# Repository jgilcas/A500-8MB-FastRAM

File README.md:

# A500-8MB-FastRAM

Okay - this is a fusion of the 8MB FastRAM Board for the Amiga 500 &amp; Amiga 500+, and the 14MHz Accelerator. 

This board is based on the A600 8MB FastRAM board here: http://lvd.nedopc.com/Projects/a600_8mb/index.html and the accelerator schematic designed by Livio Plos and released into the wild in 1992.

As such, the schematic is a derivative/fork of the original designs, to accommodate it's usage in A500's (might also work in A1000's & A2000's but it's untested).

Everything has been designed to be as easy to solder as possible. Yes, it is all SMT components but these are SOIC & SOJ for the IC's and 1206 parts with hand solder pads for the capacitors and resistors. This should be easily accomplished with a cheap soldering iron like the Yihua 937D (A Hakko knockoff from china, usually costs around £40)

The code for the CPLD has been mostly unchanged from the original, just a single letter changed to reflect usage in the A500 as opposed to the A600, along with renaming the signal pins to something simpler.

There is only 16 Mb of addressable space on 68000 CPU. This board uses half of that space, residing at $200000-$9FFFFF address range. It does autoconfigure, so no need to do anything in the DOS shell.

The original design used an Altera EPM7032 5v CPLD - this has been changed for an Atmel ATF1502ASV - as these are pin-compatible replacements. 

# Bill of Materials

-= COMING SOON =-

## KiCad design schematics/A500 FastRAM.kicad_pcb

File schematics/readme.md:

This project was created in KiCad 5.1.2 - all the files you need to build this project have been added here.

You'll need the custom library files at the very least.

I've included the SPECTRA DSN export from KiCad and the Freerouter Session file as a baseline.

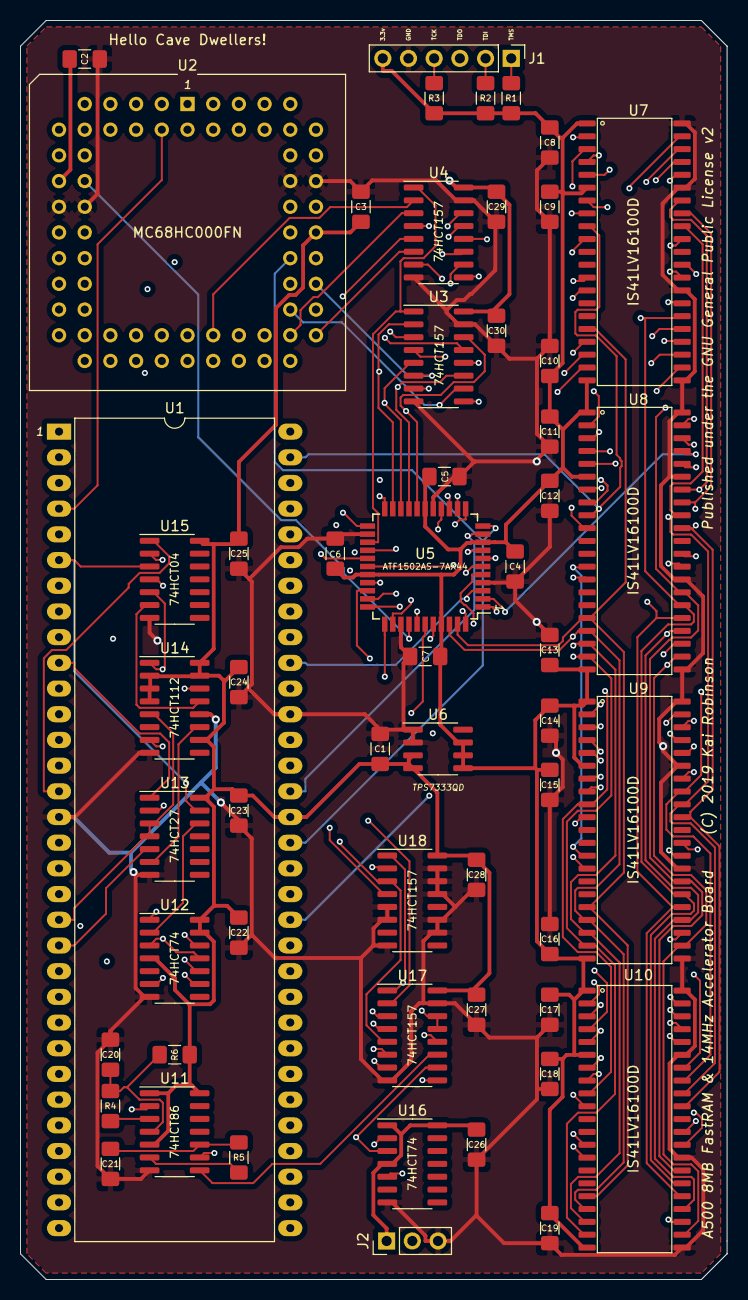
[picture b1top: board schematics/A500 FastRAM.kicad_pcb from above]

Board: 4 copper layers, 69.9 x 124.5 mm, 56 parts (0 on the bottom side), 105 nets.

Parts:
C1, C2, C3, C4, C5, C6, C7, C8, C9, C10, C11, C12, C13, C14, C15, C16, C17, C18, C19, C22, C23, C24, C25, C26, C27, C28, C29, C30: 0.1uF; C_1206_3216Metric_Pad1.42x1.75mm_HandSolder
C20, C21: 22pf; C_1206_3216Metric_Pad1.42x1.75mm_HandSolder
J1: Conn_01x06_Male; PinHeader_1x06_P2.54mm_Vertical
J2: Speed Selector; PinHeader_1x03_P2.54mm_Vertical
R1, R2, R3, R6: 10k; R_1206_3216Metric_Pad1.42x1.75mm_HandSolder
R4, R5: 560; R_1206_3216Metric_Pad1.42x1.75mm_HandSolder
U1: 68000 Boardside; DIP-64_W22.86mm_LongPads
U2: MC68000FN; PLCC-68_THT-Socket
U3, U4: 74157; SOIC-16_3.9x9.9mm_P1.27mm
U5: ATF1502AS-7AX44; TQFP-44_10x10mm_P0.8mm
U6: TPS7333QD; SOIC-8_3.9x4.9mm_P1.27mm
U7, U8, U9, U10: IS41LV16100D; SOJ-42
U11: 74HC86; SOIC-14_3.9x8.7mm_P1.27mm
U12, U16: 74HC74; SOIC-14_3.9x8.7mm_P1.27mm
U13: 74LS27; SOIC-14_3.9x8.7mm_P1.27mm
U14: 74LS112; SOIC-16_3.9x9.9mm_P1.27mm
U15: 74HC04; SOIC-14_3.9x8.7mm_P1.27mm
U17, U18: 74LS157; SOIC-16_3.9x9.9mm_P1.27mm

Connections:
/A500 FastRAM Page 3/CDAC: C21.2, R5.1, U11.10
/A500 FastRAM Page 3/SEL_SW: U16.5, U17.1, U18.1
/A500 FastRAM Page 3/SPD_SEL: J2.2, U16.2
/A500 FastRAM Page 3/SW_CLK14: U11.8, U17.11
/A500 FastRAM Page 3/SW_E14: U14.1, U15.5, U17.2
/A500 FastRAM Page 3/SW_VMA: U14.7, U17.5, U18.3
/A500 FastRAM Page 3/_CLKIN: U12.3, U12.11, U15.2
/A500 FastRAM Page 3/_E_OUT: U14.13, U15.6
/CPU_A1: U1.29, U2.32, U5.23
/CPU_A2: U1.30, U2.33, U5.22
/CPU_A3: U1.31, U2.34, U3.2, U5.21
/CPU_A4: U1.32, U2.35, U3.5, U5.20
/CPU_A5: U1.33, U2.36, U3.11, U5.19
/CPU_A6: U1.34, U2.37, U3.14, U5.18
/CPU_A7: U1.35, U2.38, U4.2
/CPU_A8: U1.36, U2.39, U4.5
/CPU_A9: U1.37, U2.40, U4.11
/CPU_A10: U1.38, U2.41, U4.14
/CPU_A11: U1.39, U2.42, U4.13
/CPU_A12: U1.40, U2.43, U4.10
/CPU_A13: U1.41, U2.44, U4.6
/CPU_A14: U1.42, U2.45, U4.3
/CPU_A15: U1.43, U2.46, U3.13
/CPU_A16: U1.44, U2.47, U3.10, U5.15
/CPU_A17: U1.45, U2.48, U3.6, U5.14
/CPU_A18: U1.46, U2.49, U3.3, U5.13
/CPU_A19: U1.47, U2.50, U5.12
/CPU_A20: U1.48, U2.51, U5.11
/CPU_A21: U1.50, U2.53, U5.10
/CPU_A22: U1.51, U2.54, U5.8
/CPU_A23: U1.52, U2.55, U5.6
/CPU_AS: U1.6, U12.12, U13.13, U15.3, U17.13, U17.14
/CPU_AS14: U2.6, U5.40, U17.12
/CPU_BERR: U1.22, U2.24
/CPU_BG: U1.11, U2.11
/CPU_BGACK: U1.12, U2.12
/CPU_BR: U1.13, U2.13
/CPU_CLK: U1.15, U11.2, U11.9, U15.1, U16.3, U17.10
/CPU_CLK14: U2.15, U5.37, U17.9
/CPU_D0: U1.5, U2.5, U7.2, U8.2, U9.2, U10.2
/CPU_D1: U1.4, U2.4, U7.3, U8.3, U9.3, U10.3
/CPU_D2: U1.3, U2.3, U7.4, U8.4, U9.4, U10.4
/CPU_D3: U1.2, U2.2, U7.5, U8.5, U9.5, U10.5
/CPU_D4: U1.1, U2.1, U7.7, U8.7, U9.7, U10.7
/CPU_D5: U1.64, U2.68, U7.8, U8.8, U9.8, U10.8
/CPU_D6: U1.63, U2.67, U7.9, U8.9, U9.9, U10.9
/CPU_D7: U1.62, U2.66, U7.10, U8.10, U9.10, U10.10
/CPU_D8: U1.61, U2.65, U7.33, U8.33, U9.33, U10.33
/CPU_D9: U1.60, U2.64, U7.34, U8.34, U9.34, U10.34
/CPU_D10: U1.59, U2.63, U7.35, U8.35, U9.35, U10.35
/CPU_D11: U1.58, U2.62, U7.36, U8.36, U9.36, U10.36
/CPU_D12: U1.57, U2.61, U5.44, U7.38, U8.38, U9.38, U10.38
/CPU_D13: U1.56, U2.60, U5.2, U7.39, U8.39, U9.39, U10.39
/CPU_D14: U1.55, U2.59, U5.3, U7.40, U8.40, U9.40, U10.40
/CPU_D15: U1.54, U2.58, U5.5, U7.41, U8.41, U9.41, U10.41
/CPU_DTACK: U1.10, U13.1
/CPU_DTACK14: U2.10, U12.6
/CPU_E: U1.20, U13.3, U13.4, U14.5, U17.3
/CPU_E14: U2.22, U17.4
/CPU_FC0: U1.28, U2.30
/CPU_FC1: U1.27, U2.29
/CPU_FC2: U1.26, U2.28
/CPU_HALT: U1.17, U2.19
/CPU_IPL0: U1.25, U2.27
/CPU_IPL1: U1.24, U2.26
/CPU_IPL2: U1.23, U2.25
/CPU_LDS: U1.8, U2.8, U5.27
/CPU_RESET: U1.18, U2.20, U5.39
/CPU_RW: U1.9, U2.9, U7.13, U8.13, U9.13, U10.13
/CPU_UDS: U1.7, U2.7, U5.38
/CPU_VMA: U1.19, U18.2
/CPU_VMA14: U2.21, U18.4
/CPU_VPA: U1.21, U13.5, U17.6
/CPU_VPA14: U2.23, U17.7
/DRAM_A0: U5.43, U7.17, U8.17, U9.17, U10.17
/DRAM_A1: U5.42, U7.18, U8.18, U9.18, U10.18
/DRAM_A2: U3.4, U7.19, U8.19, U9.19, U10.19
/DRAM_A3: U3.7, U7.20, U8.20, U9.20, U10.20
/DRAM_A4: U3.9, U7.23, U8.23, U9.23, U10.23
/DRAM_A5: U3.12, U7.24, U8.24, U9.24, U10.24
/DRAM_A6: U4.4, U7.25, U8.25, U9.25, U10.25
/DRAM_A7: U4.7, U7.26, U8.26, U9.26, U10.26
/DRAM_A8: U4.9, U7.27, U8.27, U9.27, U10.27
/DRAM_A9: U4.12, U7.28, U8.28, U9.28, U10.28
/DRAM_LCAS: U5.33, U7.31, U8.31, U9.31, U10.31
/DRAM_RAS0: U5.28, U7.14
/DRAM_RAS1: U5.30, U8.14
/DRAM_RAS2: U5.31, U9.14
/DRAM_RAS3: U5.34, U10.14
/DRAM_UCAS: U5.35, U7.30, U8.30, U9.30, U10.30
/MUX_SWITCH: U3.1, U4.1, U5.25
/TCK: J1.4, R3.2, U5.26
/TDI: J1.2, R2.2, U5.1
/TDO: J1.3, U5.32
/TMS: J1.1, R1.2, U5.7
/VCC33: C4.2, C5.1, C6.2, C7.2, C8.1, C9.1, C10.1, C11.1, C12.1, C13.1, C14.1, C15.1, C16.1, C17.1, C18.1, C19.1, J1.6, R1.1, R2.1, R3.1, U5.9, U5.17, U5.29, U5.41, U6.5, U6.6, U6.7, U7.1, U7.6, U7.21, U8.1, U8.6, U8.21, U9.1, U9.6, U9.21, U10.1, U10.6, U10.21
GND: C1.2, C2.1, C3.1, C4.1, C5.2, C6.1, C7.1, C8.2, C9.2, C10.2, C11.2, C12.2, C13.2, C14.2, C15.2, C16.2, C17.2, C18.2, C19.2, C20.1, C21.1, C22.2, C23.2, C24.2, C25.2, C26.2, C27.2, C28.2, C29.2, C30.2, J1.5, J2.3, U1.16, U1.53, U2.16, U2.17, U2.56, U2.57, U3.8, U3.15, U4.8, U4.15, U5.4, U5.16, U5.24, U5.36, U6.1, U6.2, U7.22, U7.29, U7.37, U7.42, U8.22, U8.29, U8.37, U8.42, U9.22, U9.29, U9.37, U9.42, U10.22, U10.29, U10.37, U10.42, U11.7, U12.7, U13.7, U14.8, U14.12, U15.7, U16.7, U17.8, U17.15, U18.5, U18.6, U18.8, U18.10, U18.11, U18.13, U18.14, U18.15
unnamed: C20.2, R4.1, R6.2, U11.4
unnamed: R4.2, U11.3
unnamed: R5.2, U11.6
unnamed: U12.1, U12.10, U14.14, U15.4
unnamed: U12.2, U13.12
unnamed: U12.9, U13.2
unnamed: U13.6, U14.11
VCC: C1.1, C2.2, C3.2, C22.1, C23.1, C24.1, C25.1, C26.1, C27.1, C28.1, C29.1, C30.1, J2.1, R6.1, U1.14, U1.49, U2.14, U2.52, U3.16, U4.16, U6.3, U6.4, U11.1, U11.5, U11.14, U12.4, U12.13, U12.14, U13.14, U14.2, U14.3, U14.4, U14.10, U14.15, U14.16, U15.14, U16.1, U16.4, U16.14, U17.16, U18.16

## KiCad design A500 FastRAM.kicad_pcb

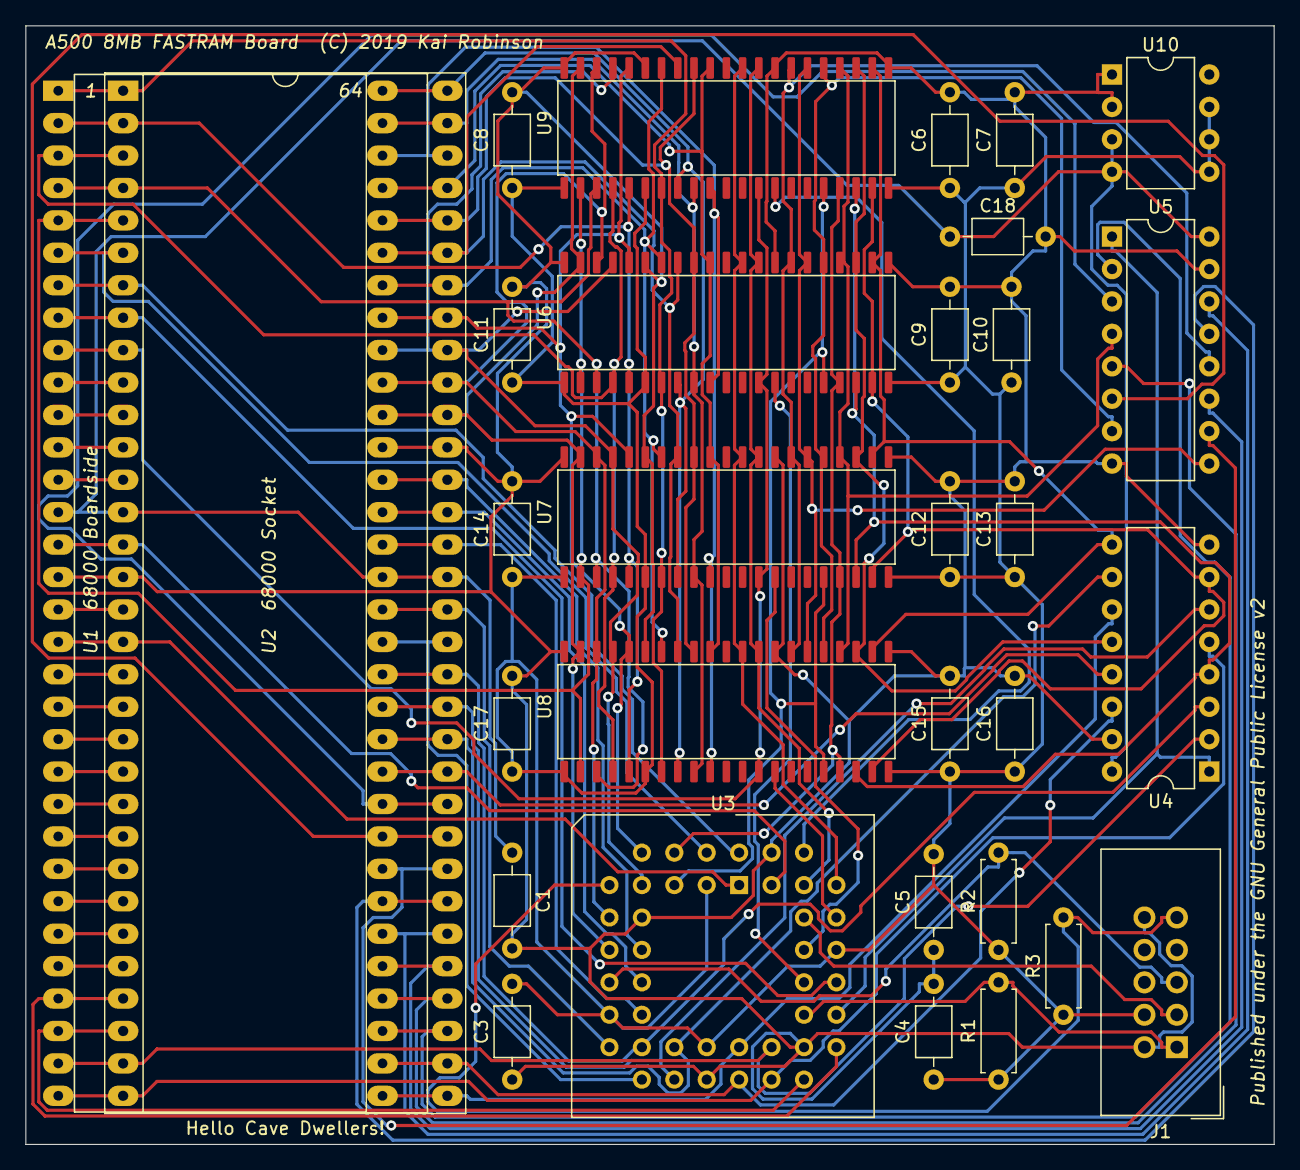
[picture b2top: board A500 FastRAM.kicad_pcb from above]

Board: 2 copper layers, 97.8 x 87.6 mm, 31 parts (0 on the bottom side), 84 nets.

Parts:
C1, C3, C4, C5, C6, C7, C8, C9, C10, C11, C12, C13, C14, C15, C16, C17, C18: 0.1uF; C_Axial_L3.8mm_D2.6mm_P7.50mm_Horizontal
J1: Microsemi_FlashPro-JTAG-10; IDC-Header_2x05_P2.54mm_Vertical
R1, R2, R3: 10k; R_Axial_DIN0207_L6.3mm_D2.5mm_P7.62mm_Horizontal
U1: 68000 Boardside; DIP-64_W25.4mm_SIL_Headers
U2: 68000 Socket; DIP-64_W25.4mm_Socket_LongPads
U3: ATF1502ASV-15JU44; PLCC-44_THT-Socket
U4, U5: 74157; DIP-16_W7.62mm
U6, U7, U8, U9: IS41LV16100D; SOJ-42
U10: TPS7333QP; DIP-8_W7.62mm

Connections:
/CPU_A1: U1.29, U2.29, U3.29
/CPU_A2: U1.30, U2.30, U3.28
/CPU_A3: U1.31, U2.31, U3.27, U4.2
/CPU_A4: U1.32, U2.32, U3.26, U4.5
/CPU_A5: U1.33, U2.33, U3.25, U4.11
/CPU_A6: U1.34, U2.34, U3.24, U4.14
/CPU_A7: U1.35, U2.35, U5.2
/CPU_A8: U1.36, U2.36, U5.5
/CPU_A9: U1.37, U2.37, U5.11
/CPU_A10: U1.38, U2.38, U5.14
/CPU_A11: U1.39, U2.39, U5.13
/CPU_A12: U1.40, U2.40, U5.10
/CPU_A13: U1.41, U2.41, U5.6
/CPU_A14: U1.42, U2.42, U5.3
/CPU_A15: U1.43, U2.43, U4.13
/CPU_A16: U1.44, U2.44, U3.21, U4.10
/CPU_A17: U1.45, U2.45, U3.20, U4.6
/CPU_A18: U1.46, U2.46, U3.19, U4.3
/CPU_A19: U1.47, U2.47, U3.18
/CPU_A20: U1.48, U2.48, U3.17
/CPU_A21: U1.50, U2.50, U3.16
/CPU_A22: U1.51, U2.51, U3.14
/CPU_A23: U1.52, U2.52, U3.12
/CPU_AS: U1.6, U2.6, U3.2
/CPU_BERR: U1.22, U2.22
/CPU_BG: U1.11, U2.11
/CPU_BGACK: U1.12, U2.12
/CPU_BR: U1.13, U2.13
/CPU_CLK: U1.15, U2.15, U3.43
/CPU_D0: U1.5, U2.5, U6.2, U7.2, U8.2, U9.2
/CPU_D1: U1.4, U2.4, U6.3, U7.3, U8.3, U9.3
/CPU_D2: U1.3, U2.3, U6.4, U7.4, U8.4, U9.4
/CPU_D3: U1.2, U2.2, U6.5, U7.5, U8.5, U9.5
/CPU_D4: U1.1, U2.1, U6.7, U7.7, U8.7, U9.7
/CPU_D5: U1.64, U2.64, U6.8, U7.8, U8.8, U9.8
/CPU_D6: U1.63, U2.63, U6.9, U7.9, U8.9, U9.9
/CPU_D7: U1.62, U2.62, U6.10, U7.10, U8.10, U9.10
/CPU_D8: U1.61, U2.61, U6.33, U7.33, U8.33, U9.33
/CPU_D9: U1.60, U2.60, U6.34, U7.34, U8.34, U9.34
/CPU_D10: U1.59, U2.59, U6.35, U7.35, U8.35, U9.35
/CPU_D11: U1.58, U2.58, U6.36, U7.36, U8.36, U9.36
/CPU_D12: U1.57, U2.57, U3.6, U6.38, U7.38, U8.38, U9.38
/CPU_D13: U1.56, U2.56, U3.8, U6.39, U7.39, U8.39, U9.39
/CPU_D14: U1.55, U2.55, U3.9, U6.40, U7.40, U8.40, U9.40
/CPU_D15: U1.54, U2.54, U3.11, U6.41, U7.41, U8.41, U9.41
/CPU_DTACK: U1.10, U2.10
/CPU_E: U1.20, U2.20
/CPU_FC0: U1.28, U2.28
/CPU_FC1: U1.27, U2.27
/CPU_FC2: U1.26, U2.26
/CPU_HALT: U1.17, U2.17
/CPU_IPL0: U1.25, U2.25
/CPU_IPL1: U1.24, U2.24
/CPU_IPL2: U1.23, U2.23
/CPU_LDS: U1.8, U2.8, U3.33
/CPU_RESET: U1.18, U2.18, U3.1
/CPU_RW: U1.9, U2.9, U6.13, U7.13, U8.13, U9.13
/CPU_UDS: U1.7, U2.7, U3.44
/CPU_VMA: U1.19, U2.19
/CPU_VPA: U1.21, U2.21
/DRAM_A0: U3.5, U6.17, U7.17, U8.17, U9.17
/DRAM_A1: U3.4, U6.18, U7.18, U8.18, U9.18
/DRAM_A2: U4.4, U6.19, U7.19, U8.19, U9.19
/DRAM_A3: U4.7, U6.20, U7.20, U8.20, U9.20
/DRAM_A4: U4.9, U6.23, U7.23, U8.23, U9.23
/DRAM_A5: U4.12, U6.24, U7.24, U8.24, U9.24
/DRAM_A6: U5.4, U6.25, U7.25, U8.25, U9.25
/DRAM_A7: U5.7, U6.26, U7.26, U8.26, U9.26
/DRAM_A8: U5.9, U6.27, U7.27, U8.27, U9.27
/DRAM_A9: U5.12, U6.28, U7.28, U8.28, U9.28
/DRAM_LCAS: U3.39, U6.31, U7.31, U8.31, U9.31
/DRAM_RAS0: U3.34, U6.14
/DRAM_RAS1: U3.36, U7.14
/DRAM_RAS2: U3.37, U8.14
/DRAM_RAS3: U3.40, U9.14
/DRAM_UCAS: U3.41, U6.30, U7.30, U8.30, U9.30
/MUX_SWITCH: U3.31, U4.1, U5.1
/TCK: J1.1, R1.2, U3.32
/TDI: J1.9, R3.2, U3.7
/TDO: J1.3, U3.38
/TMS: J1.5, R2.2, U3.13
/VCC33: C3.2, C4.1, C5.2, C6.1, C7.1, C8.1, C9.1, C10.1, C11.1, C12.1, C13.1, C14.1, C15.1, C16.1, C17.1, J1.4, R1.1, R2.1, R3.1, U3.3, U3.15, U3.23, U3.35, U6.1, U6.6, U6.21, U7.1, U7.6, U7.21, U8.1, U8.6, U8.21, U9.1, U9.6, U9.21, U10.5, U10.6, U10.7
GND: C1.2, C3.1, C4.2, C5.1, C6.2, C7.2, C8.2, C9.2, C10.2, C11.2, C12.2, C13.2, C14.2, C15.2, C16.2, C17.2, C18.2, J1.2, J1.10, U1.16, U1.53, U2.16, U2.53, U3.10, U3.22, U3.30, U3.42, U4.8, U4.15, U5.8, U5.15, U6.22, U6.29, U6.37, U6.42, U7.22, U7.29, U7.37, U7.42, U8.22, U8.29, U8.37, U8.42, U9.22, U9.29, U9.37, U9.42, U10.1, U10.2
VCC: C1.1, C18.1, U1.14, U1.49, U2.14, U2.49, U4.16, U5.16, U10.3, U10.4

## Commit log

2019-05-09 Rename A500 FastRAM.sch to schematics/A500 FastRAM.sch
2019-05-09 Rename A500 FastRAM Page 2.sch to schematics/A500 FastRAM Page 2.sch
2019-05-09 Rename A500 FastRAM.kicad_pcb to schematics/A500 FastRAM.kicad_pcb
2019-05-09 Rename A500 FastRAM.pro to schematics/A500 FastRAM.pro
2019-05-09 Rename A500 FastRAM.dsn to schematics/A500 FastRAM.dsn
2019-05-09 Rename A500 FastRAM.ses to schematics/A500 FastRAM.ses
2019-05-09 Rename A500 FastRAM Verilog.txt to code/A500 FastRAM Verilog.v
2019-05-10 Create LICENSE
2019-05-26 Add files via upload
    v1.1 - tweaking layout, compacting things a bit, better routing with less via's
2019-06-02 Version 2
    Swapped some components to SMD, reduced size of board - stepping stone to full blown accelerator integration!
2019-06-08 New & Improved ?
    Whee! Complete revamp including 14Mhz accelerator!
2019-06-08 Fixed stuff
2019-06-11 Fixing wrong CPU Socket, tweaking layout & routing
2019-06-12 Total respin

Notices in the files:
A500 FastRAM.kicad_pcb:
Published under the GNU General Public License v2
(C) 2019 Kai Robinson
